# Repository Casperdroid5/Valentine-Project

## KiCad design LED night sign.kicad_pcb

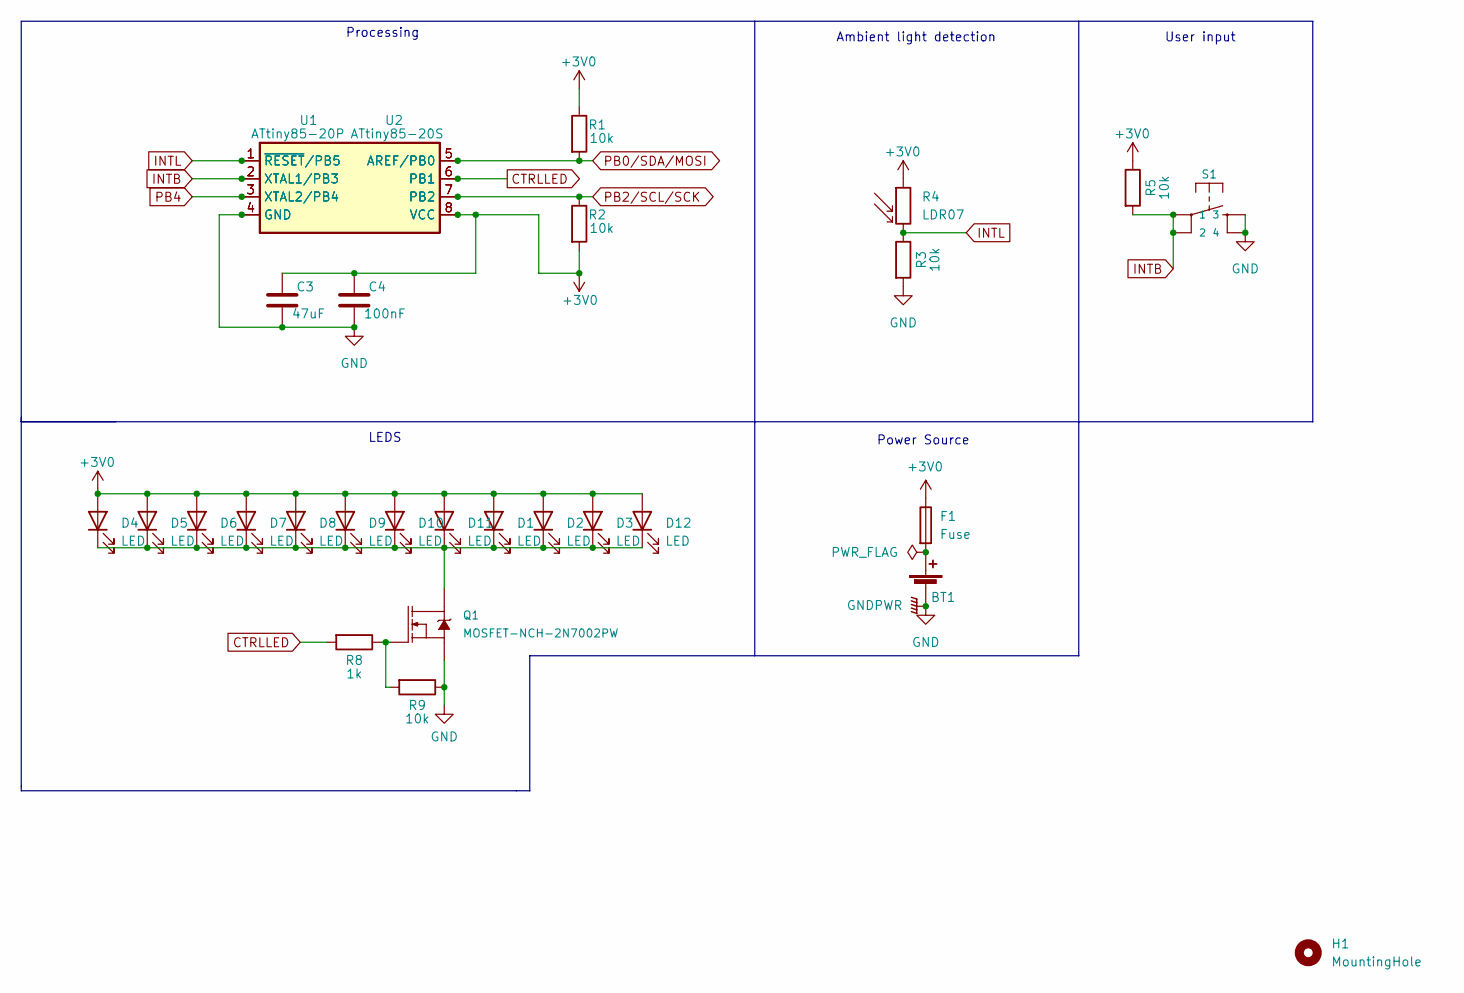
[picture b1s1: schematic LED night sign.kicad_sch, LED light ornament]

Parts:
BT1: 2032; BatteryHolder_Keystone_3002_1x2032
C3: 47uF; C_1206_3216Metric_Pad1.33x1.80mm_HandSolder
C4: 100nF; C_1206_3216Metric_Pad1.33x1.80mm_HandSolder
D1, D2, D3, D4, D5, D6, D7, D8, D9, D10, D11, D12: LED; LED_1206_3216Metric_Pad1.42x1.75mm_HandSolder
F1: Fuse; R_1206_3216Metric_Pad1.30x1.75mm_HandSolder
H1: MountingHole; MountingHole_2.5mm
Q1: MOSFET-NCH-2N7002PW; SOT96P240X120-3N
R1, R2, R3, R5, R9: 10k; R_1206_3216Metric_Pad1.30x1.75mm_HandSolder
R4: LDR07; R_LDR_5.1x4.3mm_P3.4mm_Vertical
R8: 1k; R_1206_3216Metric_Pad1.30x1.75mm_HandSolder
S1: MOMENTARY-SWITCH-SPST-2-SMD-5.2MM; SW_SPST_TL3305B
U1: ATtiny85-20P; DIP781W56P254L950H533Q8N
U2: ATtiny85-20S; SOIC-8W_5.3x5.3mm_P1.27mm

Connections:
+3V0: C3.1, C4.1, D1.2 (A), D2.2 (A), D3.2 (A), D4.2 (A), D5.2 (A), D6.2 (A), D7.2 (A), D8.2 (A), D9.2 (A), D10.2 (A), D11.2 (A), D12.2 (A), F1.1, R1.1, R2.2, R4.1, R5.1, U1.8 (VCC), U2.8 (VCC)
CTRLLED: R8.2, U1.6 (PB1), U2.6 (PB1)
GND: BT1.2 (-), C3.2, C4.2, Q1.2 (S), R3.2, R9.1, S1.3, S1.4, U1.4 (GND), U2.4 (GND)
INTB: R5.2, S1.1, S1.2, U1.2 (XTAL1/PB3), U2.2 (XTAL1/PB3)
INTL: R3.1, R4.2, U1.1 (~RESET/PB5), U2.1 (~RESET/PB5)
unnamed: BT1.1 (+), F1.2
unnamed: D1.1 (K), D2.1 (K), D3.1 (K), D4.1 (K), D5.1 (K), D6.1 (K), D7.1 (K), D8.1 (K), D9.1 (K), D10.1 (K), D11.1 (K), D12.1 (K), Q1.3 (D)
unnamed: Q1.1 (G), R8.1, R9.2
PB0/SDA/MOSI: R1.2, U1.5 (AREF/PB0), U2.5 (AREF/PB0)
PB2/SCL/SCK: R2.1, U1.7 (PB2), U2.7 (PB2)
PB4: U1.3 (XTAL2/PB4), U2.3 (XTAL2/PB4)

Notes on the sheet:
LEDS
Processing
Power Source
User input
Ambient light detection

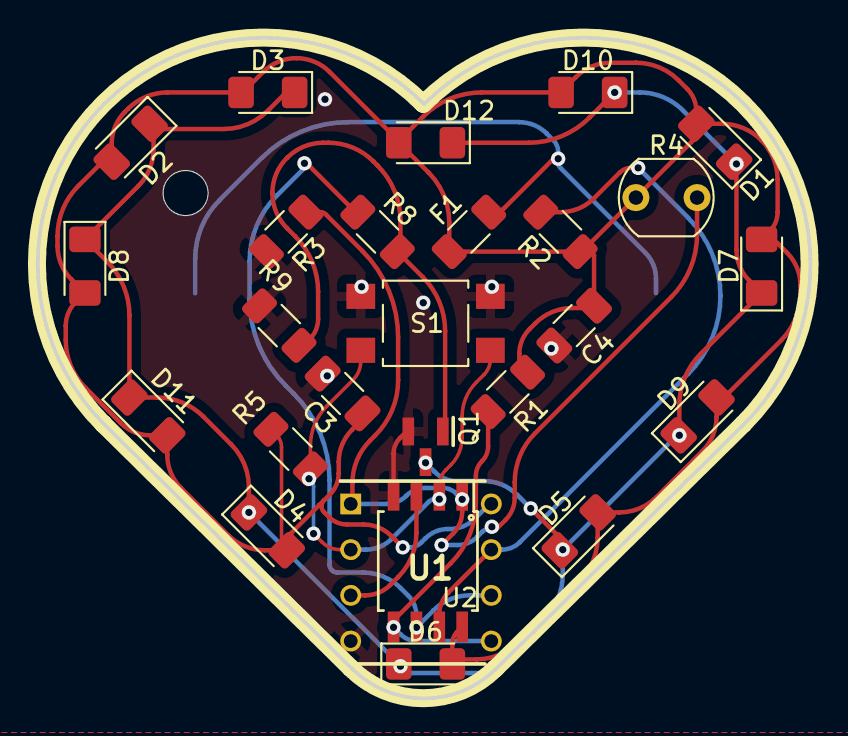
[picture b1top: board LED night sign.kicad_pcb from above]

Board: 2 copper layers, 42.9 x 36.7 mm, 28 parts (1 on the bottom side), 11 nets.

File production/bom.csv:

Designator,Footprint,Quantity,Value,LCSC Part #
BT1,BatteryHolder_Keystone_3002_1x2032,1,2032,
C3,C_1206_3216Metric_Pad1.33x1.80mm_HandSolder,1,47uF,
C4,C_1206_3216Metric_Pad1.33x1.80mm_HandSolder,1,100nF,
"D1, D10, D11, D12, D2, D3, D4, D5, D6, D7, D8, D9",LED_1206_3216Metric_Pad1.42x1.75mm_HandSolder,12,LED,
F1,R_1206_3216Metric_Pad1.30x1.75mm_HandSolder,1,Fuse,
Q1,SOT96P240X120-3N,1,MOSFET-NCH-2N7002PW,
"R1, R2, R3, R5, R9",R_1206_3216Metric_Pad1.30x1.75mm_HandSolder,5,10k,
R4,R_LDR_5.1x4.3mm_P3.4mm_Vertical,1,LDR07,
R8,R_1206_3216Metric_Pad1.30x1.75mm_HandSolder,1,1k,
S1,SW_SPST_TL3305B,1,MOMENTARY-SWITCH-SPST-2-SMD-5.2MM,
U1,DIP781W56P254L950H533Q8N,1,ATtiny85-20P,
U2,SOIC-8W_5.3x5.3mm_P1.27mm,1,ATtiny85-20S,

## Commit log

2022-09-30 First prototype
2022-09-30 enh schematic and added pdf
2022-09-30 Enh pcb layout
    repositioned leds to be more symmetrical
    improved silkscreens
2022-09-30 made room for potential holes
2022-09-30 melted the circuit (rounded tracks)
2022-10-01 enh pcb and sch
2022-10-01 Improved pcb wiring
2022-10-01 Finished V1.0
2022-10-01 fixed silkscreen
2022-10-01 changed ic for light sensing
2022-10-01 ready for order
2022-10-09 cleanup
2022-11-08 Improved design and added 3D models
2022-11-21 component placement done and starting wiring
2022-11-21 moved components a bit down.
2022-11-21 centered components
2022-11-21 added silkscreen
2022-11-22 added push button
2022-11-22 added rounded traces and production
2022-12-15 added mounting hole (for keychain)
2022-12-15 added dot to silkscreen for orientation (u2)
